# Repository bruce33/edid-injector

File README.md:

A simple board with edid EEPROM for HDMI video cables.

# Other parts

## Connectors

 * HDMI connectors
  * **With** locking screw flange
   * `CONN RCPT HDMI W/FLANGE R/A SMD`
   * Manufacture part number: [FCI 10029449-002TLF]
   * Digikey part number: [609-1011-ND](http://www.digikey.com/product-search/en?KeyWords=609-1011-ND&WT.z_header=search_go)
   * [Datasheet](http://portal.fciconnect.com/Comergent//fci/drawing/10029449.pdf)
   * 
   * Cost: $1.17 USD in individual quantities.

  * **Without** locking screw flange.
   * `CONN HDMI RECPT 19POS SMT R/A`
   * Manufacture part number: [FCI 10029449-111RLF]
   * Digikey part number: [609-4614-1-ND](http://www.digikey.com/product-detail/en/10029449-111RLF/609-4614-1-ND/2785376)
   * [Datasheet](http://portal.fciconnect.com/Comergent//fci/drawing/10029449.pdf)
   * 
   * Cost: $0.73 USD in individual quantities.

# Editing

The designs in this repository was made using
[KiCad](http://www.kicad-pcb.org/) version **4.0.7**.

# License

Creative Commons Attribution-ShareAlike 4.0 International License.

You should have received a copy of the license along with this
work.  If not, see <http://creativecommons.org/licenses/by-sa/4.0/>.

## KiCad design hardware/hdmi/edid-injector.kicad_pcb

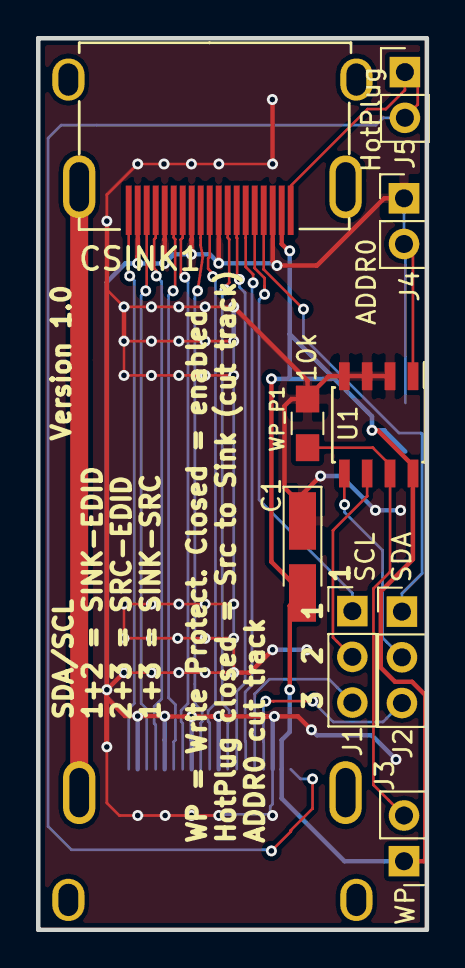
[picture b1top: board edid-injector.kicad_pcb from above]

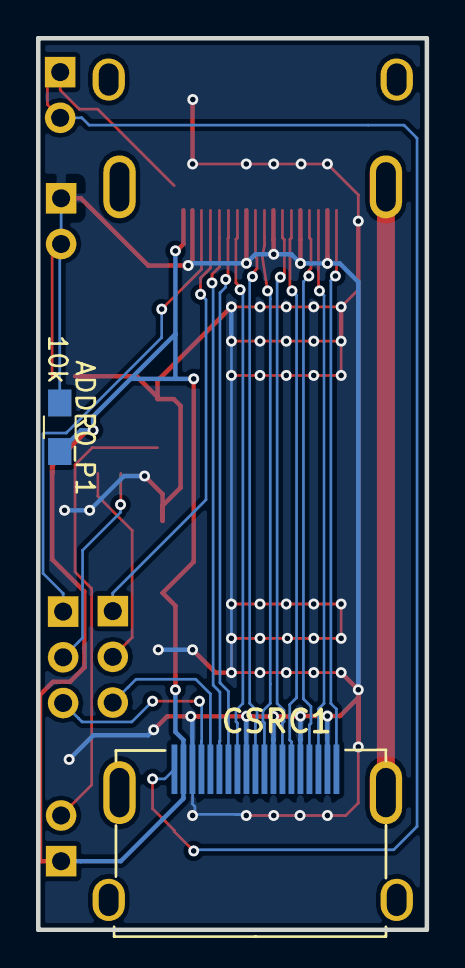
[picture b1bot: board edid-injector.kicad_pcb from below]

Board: 2 copper layers, 21.6 x 49.5 mm, 11 parts (2 on the bottom side), 22 nets.

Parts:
ADDR0_P1: 10k; R_0805_HandSoldering
C1: C_PWR; CP_Tantalum_Case-A_EIA-3216-18_Hand
CSINK1: HDMI; hdmi
CSRC1: HDMI; hdmi
J1: SCL; Pin_Header_Straight_1x03_Pitch2.54mm
J2: SDA; Pin_Header_Straight_1x03_Pitch2.54mm
J3: WP; Pin_Header_Straight_1x02_Pitch2.54mm
J4: ADDR0; Pin_Header_Straight_1x02_Pitch2.54mm
J5: HotPlug; Pin_Header_Straight_1x02_Pitch2.54mm
U1: 24LC16; SOIC-8_3.9x4.9mm_Pitch1.27mm
WP_P1: 10k; R_0805_HandSoldering

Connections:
/CLK+: CSINK1.10, CSRC1.10
/CLK-: CSINK1.12, CSRC1.12
/D0+: CSINK1.7, CSRC1.7
/D0-: CSINK1.9, CSRC1.9
/D1+: CSINK1.4, CSRC1.4
/D1-: CSINK1.6, CSRC1.6
/D2+: CSINK1.1, CSRC1.1
/D2-: CSINK1.3, CSRC1.3
/RES: CSINK1.14, CSRC1.14
/SINK_CEC: CSINK1.13, CSRC1.13
/SINK_HPD: CSINK1.19, J5.1
/SINK_SCL: CSINK1.15, J1.1
/SINK_SDA: CSINK1.16, J2.1
/SRC_HPD: CSRC1.19, J5.2
/SRC_SCL: CSRC1.15, J1.3
/SRC_SDA: CSRC1.16, J2.3
/VHDMI: ADDR0_P1.2, C1.2, CSINK1.18, CSRC1.18, J3.1, U1.8
GND: C1.1, CSINK1.2, CSINK1.5, CSINK1.8, CSINK1.11, CSINK1.17, CSRC1.2, CSRC1.5, CSRC1.8, CSRC1.11, CSRC1.17, J4.1, U1.2, U1.3, U1.4, WP_P1.1
unnamed: ADDR0_P1.1, J4.2, U1.1
unnamed: J1.2, U1.6
unnamed: J2.2, U1.5
unnamed: J3.2, U1.7, WP_P1.2

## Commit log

2017-12-06 Version 1.0 of simple edid eeprom
